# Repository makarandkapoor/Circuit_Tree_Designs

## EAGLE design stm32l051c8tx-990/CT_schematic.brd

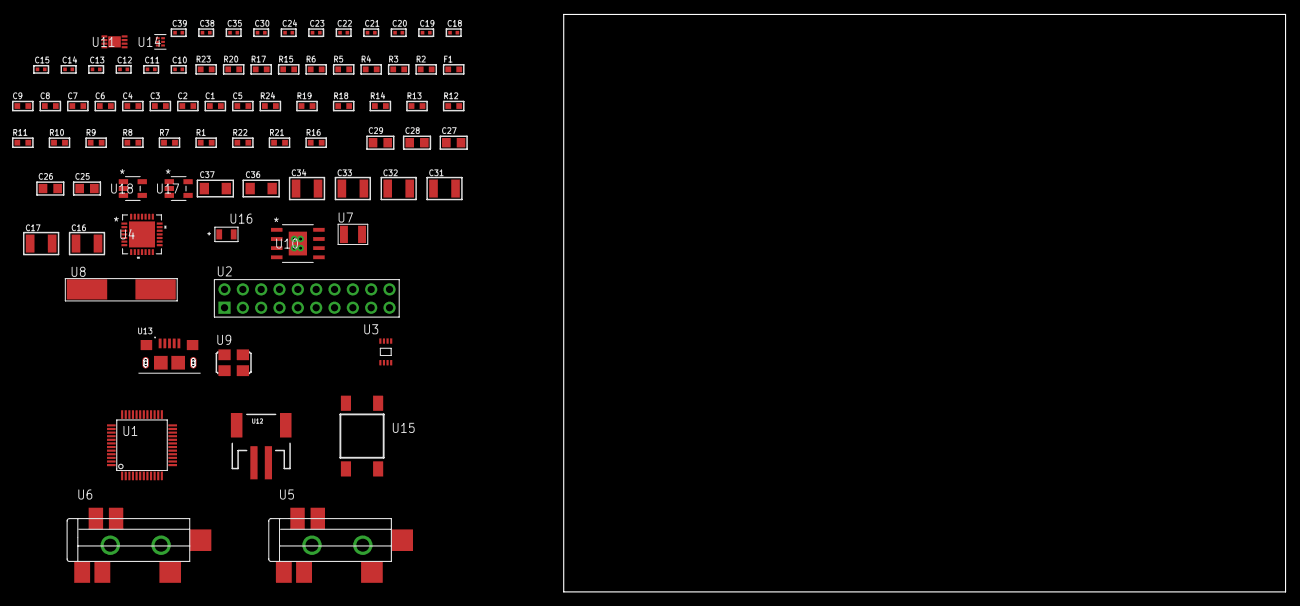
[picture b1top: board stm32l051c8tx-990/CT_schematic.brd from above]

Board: 2 copper layers, 82 parts (0 on the bottom side), 37 nets, no tracks yet.

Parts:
C1, C2, C3, C4, C6, C7: 1e-07; C0603
C5: 4.7e-06; C0603
C8: 1e-08; C0603
C9: 1e-06; C0603
C10, C11, C12, C13: 1e-11; C0402
C14, C20, C21, C22, C23, C24, C35: 1e-07; C0402
C15, C30, C38, C39: 1e-08; C0402
C16, C17: 2.2e-05; C1210
C18, C19: 1e-09; C0402
C25, C26, C27, C28, C29: 1e-05; C0805
C31, C32, C33, C34: 1e-05; C1210
C36, C37: 1e-05; C1206
F1: 240.0; L0603
R1, R7, R8, R9, R10, R11, R18, R19, R24: 10000.0; R0603
R2: 1000.0; R0603
R3: 1600.5; R0603
R4: 4700.0; R0603
R5, R6, R17: 2200.0; R0603
R12, R13, R14: 47000.0; R0603
R15: 680.0; R0603
R16: 4031.5447154472; R0603
R20: 9100.0; R0603
R21: 680000.0; R0603
R22: 120000.0; R0603
R23: 2000.0; R0603
U1: STM32L051C8T3; LQFP48
U2: TST-110-05-T-D-RA
U3: 24AA128T-I/MNY; TDFN-8/6MM
U4: WM8731CLSEFL; QFN-28
U5, U6: SJ-43515TS-SMT-TR
U7: ABS07-32.768KHZ-7-T
U8: ABLS-25.000MHZ-B2F-T
U9: ASFL1-12.288MHZ-EC-T; ASFL1
U10: MIC5234YME; SOIC-8_EP
U11: MCP73831T-2ACI/MC; DFN8_2X3MC
U12: S2B-PH-SM4-TB(LF)(SN); JST-2-SMD
U13: 10118193-0001LF; FCI_10118193-0001LF
U14: TPS3895ADRYR; SON-6
U15: 4-1437565-2; SW_4-1437565-2
U16: Q65110A2395; LGM67K-G1J2-24-Z
U17, U18: nc7sz125m5x; NC7SZ125M5X

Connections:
CLK_CRYSTAL_U1_3: C10.1, U1.3, U7.1
CLK_CRYSTAL_U1_4: C11.1, U1.4, U7.2
CLK_CRYSTAL_U1_5: C12.1, U1.5, U8.1
CLK_CRYSTAL_U1_6: C13.1, U1.6, U8.2
CLK_U4_1: U4.1, U9.3
GND: C1.2, C2.2, C3.2, C4.2, C5.2, C6.2, C7.2, C8.2, C9.2, C10.2, C11.2, C12.2, C13.2, C14.2, C15.2, C19.2, C20.2, C21.2, C22.2, C23.2, C24.2, C25.2, C26.2, C27.2, C28.2, C29.2, C30.2, C31.2, C32.2, C33.2, C34.2, C35.2, C36.2, C37.2, C38.2, C39.2, R2.2, R7.2, R9.2, R10.2, R12.2, R13.2, R14.2, R17.2, R20.2, R22.2, R23.2, U1.8, U1.23, U1.35, U1.47, U2.4, U2.6, U2.8, U2.10, U2.12, U2.14, U2.16, U2.18, U2.20, U3.4, U4.4, U4.15, U4.19, U4.25, U4.26, U4.29, U5.1, U6.1, U9.2, U10.7, U10.EPAD, U11.6, U11.9, U12.2, U13.5, U13.6, U13.7, U13.8, U13.9, U14.2, U16.C, U17.2, U17.3, U18.1, U18.3
INPUT_USBPOWER_5V: C36.1, R24.2, U11.1, U11.2, U13.1
NET_U1_7: R4.1, U1.7, U18.4
NET_U1_9: C8.1, C9.1, F1.1, U1.9
NET_U1_36: C6.1, C7.1, U1.36
NET_U1_42: R5.1, U1.42, U3.6
NET_U1_43: R6.1, U1.43, U3.5
NET_U1_44: R7.1, U1.44
NET_U1_45: R3.1, U1.45, U16.A
NET_U1_46: R1.1, U1.46, U15.3, U15.4
NET_U3_1: R9.1, U3.1
NET_U3_2: R10.1, U3.2
NET_U3_3: R11.1, U3.3
NET_U4_20: C24.1, C29.1, U4.20
NET_U5_2: C17.1, R13.1, U5.2
NET_U5_5: C16.1, R12.1, U5.5
NET_U6_5: C18.1, C19.1, R14.1, R15.1, U6.5
NET_U10_4: R16.2, R17.1, U10.4
NET_U11_5: R24.1, U11.5
NET_U11_8: R23.1, U11.8
NET_U14_1: R19.1, R20.1, U14.1
NET_U14_3: R21.2, R22.1, U14.3
NET_U14_4: R18.1, U14.4, U17.4, U18.2
NET_U15_1: R2.1, U15.1, U15.2
PROC_I2S2_CK: U1.26, U4.7
PROC_I2S2_SD: U1.28, U4.8
PROC_I2S2_WS: U1.25, U4.9, U4.11
PROC_SYS_SWCLK: U1.37, U2.9
PROC_SYS_SWDIO: U1.34, U2.7
RST_OUT_U2_SRESET_B: R8.1, U2.15, U17.1
VCC_S1_3V7: C31.1, C32.1, C37.1, U10.5, U10.8, U11.3, U11.4, U12.1
VCC_TIER1_3V3: C1.1, C2.1, C3.1, C4.1, C5.1, C14.1, C15.1, C20.1, C21.1, C22.1, C23.1, C25.1, C26.1, C27.1, C28.1, C30.1, C33.1, C34.1, C35.1, C38.1, C39.1, F1.2, R1.2, R3.2, R4.2, R5.2, R6.2, R8.2, R11.2, R16.1, R18.2, R19.2, R21.1, U1.1, U1.24, U1.48, U2.1, U3.7, U3.8, U4.3, U4.5, U4.12, U4.18, U9.4, U10.1, U14.6, U17.5, U18.5

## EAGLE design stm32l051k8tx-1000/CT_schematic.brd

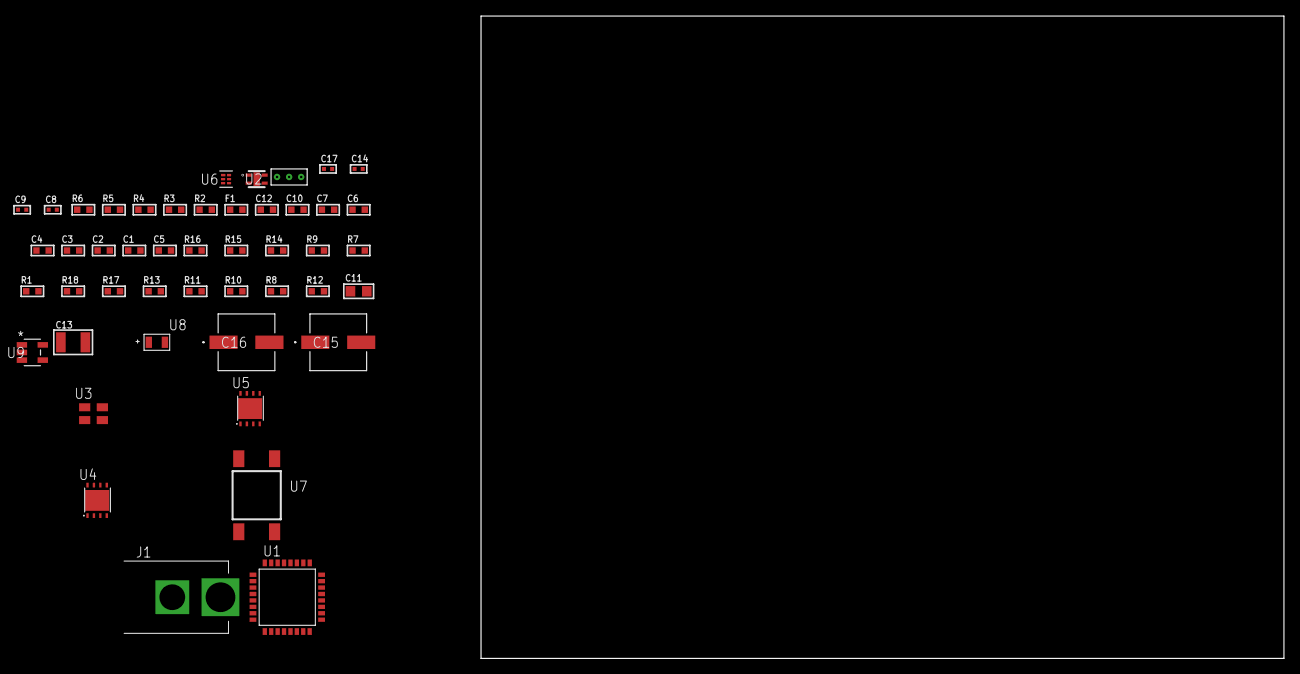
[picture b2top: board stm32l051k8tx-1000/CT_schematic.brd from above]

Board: 2 copper layers, 100.0 x 80.0 mm, 47 parts (0 on the bottom side), 22 nets, no tracks yet.

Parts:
C1, C2, C3, C4: 1e-07; C0603
C5: 4.7e-06; C0603
C6: 1e-08; C0603
C7: 1e-06; C0603
C8, C14: 1e-07; C0402
C9, C17: 1e-08; C0402
C10, C12: 8e-07; R0603
C11: 1e-05; C0805
C13: 1e-05; C1210
C15, C16: 0.0001; EXV-9H
F1: 240.0; L0603
J1: PJ-037B; PJ-037B_PACKAGE
R1, R7, R14, R15: 10000.0; R0603
R2: 1000.0; R0603
R3: 910.0; R0603
R4: 4700.0; R0603
R5, R6: 2200.0; R0603
R8, R10, R11, R13: 100000.0; R0603
R9: 36000.0; R0603
R12: 153694.38; R0603
R16: 82000.0; R0603
R17: 300000.0; R0603
R18: 120000.0; R0603
U1: STM32L051K8T6; LQFP32
U2: Si7034-A10-IM; SI7034-A10-IM
U3: ASEK-32.768KHz-ECST; ASEK
U4, U5: LP2951ACSDX/NOPB; WSON-8
U6: TPS3895ADRYR; SON-6
U7: 4-1437565-2; SW_4-1437565-2
U8: Q65110A2395; LGM67K-G1J2-24-Z
U9: nc7sz125m5x; NC7SZ125M5X
U10: Dummy; DUMMY_PACKAGE_99

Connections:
CLK_U1_2: U1.2, U3.3
GND: C1.2, C2.2, C3.2, C4.2, C5.2, C6.2, C7.2, C8.2, C9.2, C10.2, C11.2, C12.2, C13.2, C14.2, C15.2, C16.2, C17.2, J1.2, R2.2, R7.2, R10.2, R13.2, R16.2, R18.2, U1.16, U1.32, U2.5, U3.2, U4.3, U4.4, U4.PAD, U5.3, U5.4, U5.PAD, U6.2, U8.C, U9.1, U9.3, U10.1
NET_U1_4: R4.1, U1.4, U9.4
NET_U1_5: C6.1, C7.1, F1.1, U1.5
NET_U1_27: R3.1, U1.27, U8.A
NET_U1_28: R1.1, U1.28, U7.3, U7.4
NET_U1_29: R5.1, U1.29, U2.2
NET_U1_30: R6.1, U1.30, U2.4
NET_U1_31: R7.1, U1.31
NET_U4_5: R8.1, U4.5
NET_U4_7: R9.2, R10.1, U4.7
NET_U5_5: R11.1, U5.5
NET_U5_7: R12.2, R13.1, U5.7
NET_U6_1: R15.1, R16.1, U6.1
NET_U6_3: R17.2, R18.1, U6.3
NET_U6_4: R14.1, U6.4, U9.2
NET_U7_1: R2.1, U7.1, U7.2
PROC_ADC_IN4: U1.10, U10.2
PROC_ADC_IN6: U1.12, U10.3
VCC_S1_15V5: C10.1, C12.1, C15.1, C16.1, J1.1, U4.8, U5.8
VCC_TIER1_1V8: C1.1, C2.1, C3.1, C4.1, C5.1, C8.1, C11.1, C14.1, C17.1, F1.2, R1.2, R3.2, R4.2, R5.2, R6.2, R8.2, R9.1, R14.2, R15.2, R17.1, U1.1, U1.17, U2.1, U4.1, U6.6, U9.5
VCC_TIER1_3V3: C9.1, C13.1, R11.2, R12.1, U3.4, U5.1

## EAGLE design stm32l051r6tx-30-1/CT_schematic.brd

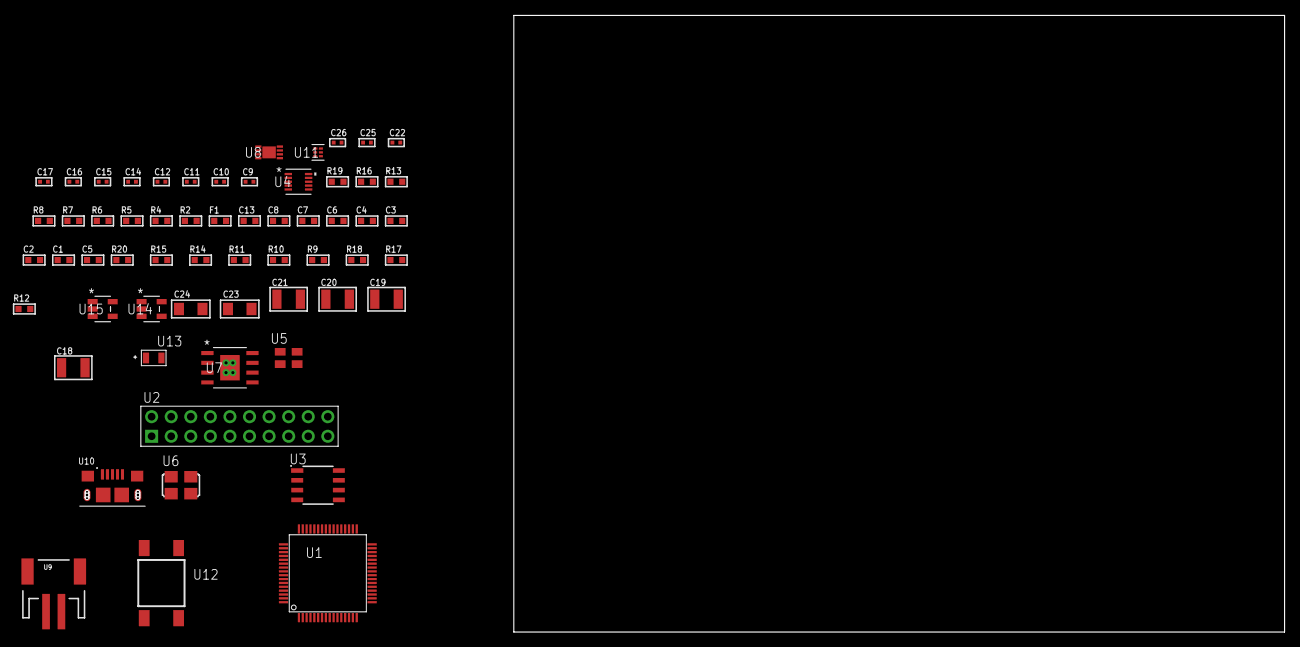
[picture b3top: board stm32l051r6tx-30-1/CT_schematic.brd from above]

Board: 2 copper layers, 155.6 x 80.0 mm, 60 parts (0 on the bottom side), 27 nets, no tracks yet.

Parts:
C1, C2, C3, C4, C6: 1e-07; C0603
C5: 4.7e-06; C0603
C7: 1e-08; C0603
C8, C13: 1e-06; C0603
C9, C11, C12, C14, C15, C22: 1e-07; C0402
C10, C16, C17, C25, C26: 1e-08; C0402
C18, C19, C20, C21: 1e-05; C1210
C23, C24: 1e-05; C1206
F1: 240.0; L0603
R2: 1000.0; R0603
R4: 4700.0; R0603
R5, R6, R7, R8, R13: 2200.0; R0603
R9, R10, R11, R14, R15, R20: 10000.0; R0603
R12: 4031.5447154472; R0603
R16: 9100.0; R0603
R17: 680000.0; R0603
R18: 120000.0; R0603
R19: 2000.0; R0603
U1: STM32L051R6T6; LQFP64
U2: TST-110-05-T-D-RA
U3: M24M02-DRMN6TP; SOIC-8
U4: MAG3110FCR1; DFN-10
U5: ASEK-32.768KHz-ECST; ASEK
U6: ASFL1-25MHZ-NCS; ASFL1
U7: MIC5234YME; SOIC-8_EP
U8: MCP73831T-2ACI/MC; DFN8_2X3MC
U9: S2B-PH-SM4-TB(LF)(SN); JST-2-SMD
U10: 10118193-0001LF; FCI_10118193-0001LF
U11: TPS3895ADRYR; SON-6
U12: 4-1437565-2; SW_4-1437565-2
U13: Q65110A2395; LGM67K-G1J2-24-Z
U14, U15: nc7sz125m5x; NC7SZ125M5X

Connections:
CLK_U1_3: U1.3, U5.3
CLK_U1_5: U1.5, U6.3
GND: C1.2, C2.2, C3.2, C4.2, C5.2, C6.2, C7.2, C8.2, C9.2, C10.2, C11.2, C12.2, C13.2, C14.2, C15.2, C16.2, C17.2, C18.2, C19.2, C20.2, C21.2, C22.2, C23.2, C24.2, C25.2, C26.2, R2.2, R9.2, R11.2, R13.2, R16.2, R18.2, R19.2, U1.12, U1.18, U1.31, U1.47, U1.63, U2.4, U2.6, U2.8, U2.10, U2.12, U2.14, U2.16, U2.18, U2.20, U3.4, U4.5, U4.10, U5.2, U6.2, U7.7, U7.EPAD, U8.6, U8.9, U9.2, U10.5, U10.6, U10.7, U10.8, U10.9, U11.2, U13.C, U14.2, U14.3, U15.1, U15.3
INPUT_USBPOWER_5V: C23.1, R20.2, U8.1, U8.2, U10.1
NET_U1_7: R4.1, U1.7, U15.4
NET_U1_13: C7.1, C8.1, F1.1, U1.13
NET_U1_29: R7.1, U1.29, U3.6
NET_U1_30: R8.1, U1.30, U3.5
NET_U1_58: R5.1, U1.58, U4.7
NET_U1_59: R6.1, U1.59, U4.6
NET_U1_60: R9.1, U1.60
NET_U1_62: U12.3, U12.4
NET_U3_3: R11.1, U3.3
NET_U4_1: C11.1, U4.1
NET_U4_4: C14.1, U4.4
NET_U7_4: R12.2, R13.1, U7.4
NET_U8_5: R20.1, U8.5
NET_U8_8: R19.1, U8.8
NET_U11_1: R15.1, R16.1, U11.1
NET_U11_3: R17.2, R18.1, U11.3
NET_U11_4: R14.1, U11.4, U14.4, U15.2
NET_U12_1: R2.1, U12.1, U12.2
PROC_SYS_SWCLK: U1.49, U2.9
PROC_SYS_SWDIO: U1.46, U2.7
RST_OUT_U2_SRESET_B: R10.1, U2.15, U14.1
VCC_S1_3V7: C18.1, C19.1, C24.1, U7.5, U7.8, U8.3, U8.4, U9.1
VCC_TIER1_3V3: C1.1, C2.1, C3.1, C4.1, C5.1, C6.1, C9.1, C10.1, C12.1, C13.1, C15.1, C16.1, C17.1, C20.1, C21.1, C22.1, C25.1, C26.1, F1.2, R4.2, R5.2, R6.2, R7.2, R8.2, R10.2, R12.1, R14.2, R15.2, R17.1, U1.1, U1.19, U1.32, U1.48, U1.64, U2.1, U3.8, U4.2, U4.8, U5.4, U6.4, U7.1, U11.6, U14.5, U15.5

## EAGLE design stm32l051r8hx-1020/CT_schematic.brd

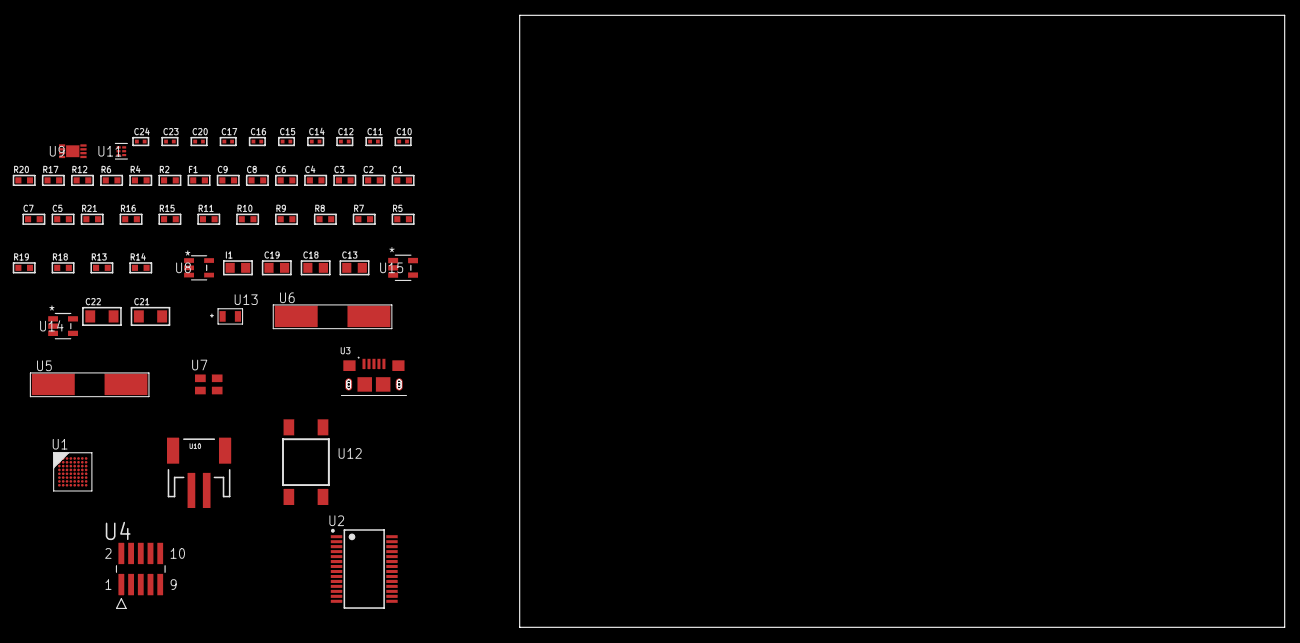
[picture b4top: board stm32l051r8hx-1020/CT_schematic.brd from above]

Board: 2 copper layers, 122.6 x 80.0 mm, 60 parts (0 on the bottom side), 35 nets, no tracks yet.

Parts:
C1, C2, C3, C4, C6: 1e-07; C0603
C5, C7: 4.7e-06; C0603
C8: 1e-08; C0603
C9: 1e-06; C0603
C10, C11: 1e-11; C0402
C12, C14, C15, C16, C20: 1e-07; C0402
C13: 4.7e-06; C0805
C17, C23, C24: 1e-08; C0402
C18, C19: 1e-05; C0805
C21, C22: 1e-05; C1206
F1: 240.0; L0603
I1: 2.2e-06; L0805
R2: 1000.0; R0603
R4, R6: 4700.0; R0603
R5, R7, R8, R9, R10, R11, R15, R16, R21: 10000.0; R0603
R12: 5.0; R0603
R13: 220000.0; R0603
R14: 1000000.0; R0603
R17: 9100.0; R0603
R18: 680000.0; R0603
R19: 120000.0; R0603
R20: 2000.0; R0603
U1: STM32L051R8H7; TFBGA64
U2: FT232RL-REEL; SSOP-28
U3: 10118193-0001LF; FCI_10118193-0001LF
U4: FTSH-105-01-L-DV-K; SAMTEC_FTSH-105-01-L-DV-K
U5: ABLS-25.000MHZ-B2F-T
U6: ABLS-12.000MHZ-B4-T
U7: ASEK-32.768KHz-ECST; ASEK
U8: ltc3406es5; TSOT-23-5
U9: MCP73831T-2ACI/MC; DFN8_2X3MC
U10: S2B-PH-SM4-TB(LF)(SN); JST-2-SMD
U11: TPS3895ADRYR; SON-6
U12: 4-1437565-2; SW_4-1437565-2
U13: Q65110A2395; LGM67K-G1J2-24-Z
U14, U15: nc7sz125m5x; NC7SZ125M5X

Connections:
CLK_CRYSTAL_U1_C1: C10.1, U1.C1, U5.1
CLK_CRYSTAL_U1_D1: C11.1, U1.D1, U5.2
CLK_CRYSTAL_U2_27: U2.27, U6.1
CLK_CRYSTAL_U2_28: U2.28, U6.2
CLK_U1_A1: U1.A1, U7.3
GND: C1.2, C2.2, C3.2, C4.2, C5.2, C6.2, C7.2, C8.2, C9.2, C10.2, C11.2, C12.2, C13.2, C14.2, C15.2, C16.2, C17.2, C18.2, C19.1, C19.2, C20.2, C21.2, C22.2, C23.2, C24.2, R2.2, R5.2, R8.2, R12.2, R13.2, R17.2, R19.2, R20.2, U1.C2, U1.D4, U1.D5, U1.D6, U1.F1, U2.7, U2.18, U2.21, U2.25, U2.26, U3.5, U3.6, U3.7, U3.8, U3.9, U4.3, U4.5, U7.2, U8.2, U9.6, U9.9, U10.2, U11.2, U13.C, U14.2, U14.3, U15.1, U15.3
INPUT_USBPOWER_5V: C21.1, R6.1, R21.2, U3.1, U9.1, U9.2
NET_U1_B4: R5.1, U1.B4
NET_U1_E1: R4.1, U1.E1, U15.4
NET_U1_H1: C8.1, C9.1, F1.1, U1.G1, U1.H1
NET_U1_H8: U12.3, U12.4
NET_U2_14: R7.1, U2.14
NET_U2_17: C14.1, U2.17
NET_U2_19: R8.1, U2.19
NET_U3_2: U2.16, U3.2
NET_U3_3: U2.15, U3.3
NET_U4_9: R12.1, U4.9
NET_U8_3: I1.1, U8.3
NET_U8_5: R13.1, R14.1, U8.5
NET_U8_ATNET_3: I1.2, R14.2
NET_U9_5: R21.1, U9.5
NET_U9_8: R20.1, U9.8
NET_U11_1: R16.1, R17.1, U11.1
NET_U11_3: R18.2, R19.1, U11.3
NET_U11_4: R15.1, U11.4, U14.4, U15.2
NET_U12_1: R2.1, U12.1, U12.2
PROC_LPUART1_CTS: U1.G4, U2.3
PROC_LPUART1_RTS: U1.B5, U2.11
PROC_LPUART1_RX: U1.B6, U2.1
PROC_LPUART1_TX: U1.B7, U2.5
PROC_SYS_SWCLK: R10.1, U1.A7, U4.4
PROC_SYS_SWDIO: R11.1, U1.A8, U4.2
RST_OUT_U4_JTAG_RST_B: R9.1, U4.10, U14.1
VCC_S1_3V7: C18.1, C22.1, U8.4, U9.3, U9.4, U10.1
VCC_TIER1_3V3: C1.1, C2.1, C3.1, C4.1, C5.1, C6.1, C7.1, C12.1, C13.1, C15.1, C16.1, C17.1, C19.2, C20.1, C23.1, C24.1, F1.2, I1.2, R4.2, R7.2, R9.2, R10.2, R11.2, R14.2, R15.2, R16.2, R18.1, U1.B2, U1.D2, U1.E4, U1.E5, U1.E6, U2.4, U2.20, U4.1, U7.4, U11.6, U14.5, U15.5

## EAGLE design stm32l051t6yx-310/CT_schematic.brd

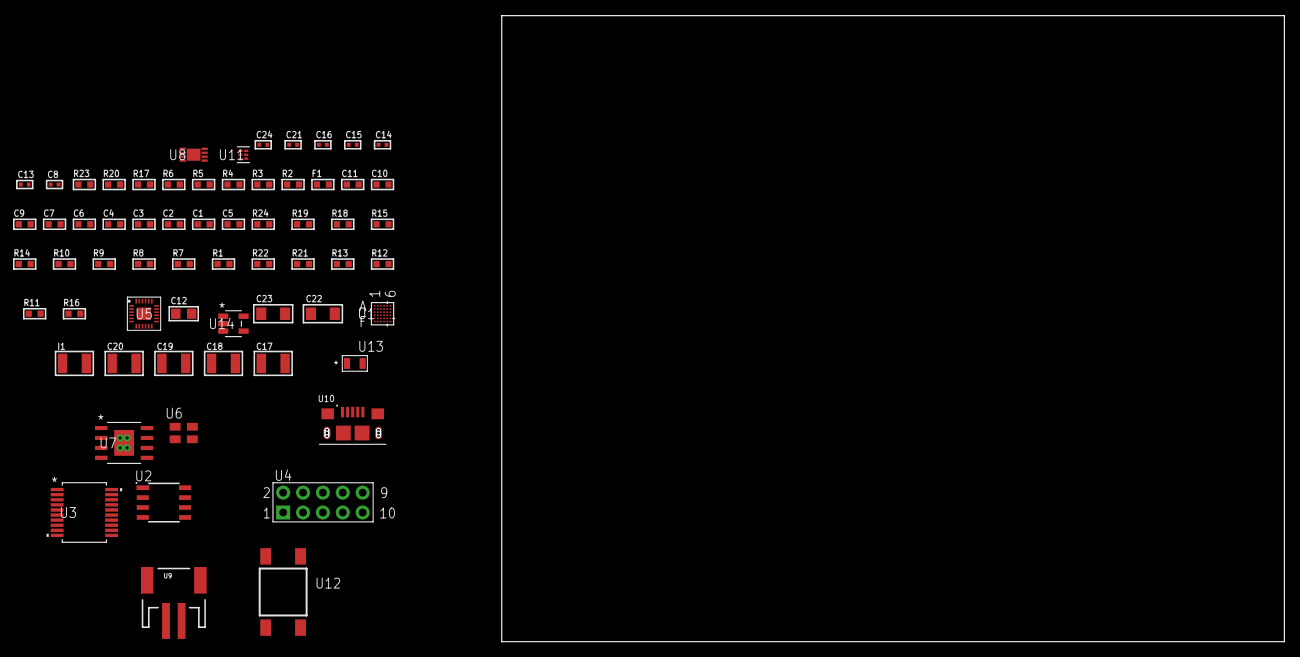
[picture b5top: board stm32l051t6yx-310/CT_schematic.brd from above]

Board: 2 copper layers, 122.6 x 80.0 mm, 64 parts (0 on the bottom side), 46 nets, no tracks yet.

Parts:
C1, C2, C3, C4: 1e-07; C0603
C5: 4.7e-06; C0603
C6: 1e-08; C0603
C7, C9, C10, C11: 1e-06; C0603
C8, C15, C16, C24: 1e-08; C0402
C12: 4.7e-06; C0805
C13, C14, C21: 1e-07; C0402
C17, C18, C19, C20: 1e-05; C1210
C22, C23: 1e-05; C1206
F1: 240.0; L0603
I1: 1.5e-05; L1210
R1, R7, R8, R9, R10, R14, R15, R18, R19, R24: 10000.0; R0603
R2: 1000.0; R0603
R3: 1600.5; R0603
R4: 4700.0; R0603
R5, R6, R17: 2200.0; R0603
R11, R12, R13: 100000.0; R0603
R16: 4031.5447154472; R0603
R20: 9100.0; R0603
R21: 680000.0; R0603
R22: 120000.0; R0603
R23: 2000.0; R0603
U1: STM32L051T6Y6TR; WLCSP36
U2: AT25256B-SSHL-T; SOIC-8
U3: MAX3218EAP+T; SSOP-20
U4: HTSS-105-01-G-D
U5: MPU-9250; QFN24_2
U6: ASEK-32.768KHz-ECST; ASEK
U7: MIC5234YME; SOIC-8_EP
U8: MCP73831T-2ACI/MC; DFN8_2X3MC
U9: S2B-PH-SM4-TB(LF)(SN); JST-2-SMD
U10: 10118193-0001LF; FCI_10118193-0001LF
U11: TPS3895ADRYR; SON-6
U12: 4-1437565-2; SW_4-1437565-2
U13: Q65110A2395; LGM67K-G1J2-24-Z
U14: nc7sz125m5x; NC7SZ125M5X

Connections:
CLK_U1_A6: U1.A6, U6.3
GND: C1.2, C2.2, C3.2, C4.2, C5.2, C6.2, C7.2, C8.2, C9.2, C10.2, C11.2, C13.2, C14.2, C15.2, C16.2, C17.2, C18.2, C19.2, C20.2, C21.2, C22.2, C23.2, C24.2, R2.2, R7.2, R17.2, R20.2, R22.2, R23.2, U1.D6, U2.4, U3.5, U3.17, U3.20, U4.9, U5.18, U5.20, U5.25, U6.2, U7.7, U7.EPAD, U8.6, U8.9, U9.2, U10.5, U10.6, U10.7, U10.8, U10.9, U11.2, U13.C, U14.1, U14.3
INPUT_USBPOWER_5V: C22.1, R24.2, U8.1, U8.2, U10.1
NET_U1_A4: R6.1, U1.A4, U5.24
NET_U1_B4: R5.1, U1.B4, U5.23
NET_U1_C5: R7.1, U1.C5
NET_U1_C6: R4.1, U1.C6, U14.4
NET_U1_D5: C6.1, C7.1, F1.1, U1.D5, U1.E6
NET_U1_F5: R3.1, U1.F5, U13.A
NET_U1_F6: R1.1, U1.F6, U12.3, U12.4
NET_U2_3: R8.1, U2.3
NET_U2_7: R10.1, U2.7
NET_U3_1: I1.1, U3.1
NET_U3_2: R11.1, U3.2
NET_U3_3: R12.1, U3.3
NET_U3_4: R13.1, U3.4
NET_U3_15: C11.1, U3.15
NET_U3_16: C12.2, U3.16
NET_U3_18: C12.1, U3.18
NET_U3_19: C10.1, U3.19
NET_U4_3: U3.12, U4.3
NET_U4_4: U3.11, U4.4
NET_U4_5: U3.14, U4.5
NET_U4_6: U3.13, U4.6
NET_U5_9: R15.1, U5.9
NET_U5_10: C13.1, U5.10
NET_U5_22: R14.1, U5.22
NET_U7_4: R16.2, R17.1, U7.4
NET_U8_5: R24.1, U8.5
NET_U8_8: R23.1, U8.8
NET_U11_1: R19.1, R20.1, U11.1
NET_U11_3: R21.2, R22.1, U11.3
NET_U11_4: R18.1, U11.4, U14.2
NET_U12_1: R2.1, U12.1, U12.2
PROC_GPIO_TO_U5_FSYNC: U1.B2, U5.11
PROC_GPIO_TO_U5_INT_B: U1.A1, U5.12
PROC_LPUART1_CTS: U1.E3, U3.8
PROC_LPUART1_RTS: U1.C3, U3.10
PROC_LPUART1_RX: U1.D2, U3.9
PROC_LPUART1_TX: U1.E2, U3.7
PROC_SPI1_MISO: U1.A3, U2.2
PROC_SPI1_MOSI: U1.B1, U2.5
PROC_SPI1_NSS: R9.1, U1.A2, U2.1
PROC_SPI1_SCK: U1.B3, U2.6
VCC_S1_3V7: C17.1, C18.1, C23.1, U7.5, U7.8, U8.3, U8.4, U9.1
VCC_TIER1_3V3: C1.1, C2.1, C3.1, C4.1, C5.1, C8.1, C9.1, C14.1, C15.1, C16.1, C19.1, C20.1, C21.1, C24.1, F1.2, I1.2, R1.2, R3.2, R4.2, R5.2, R6.2, R8.2, R9.2, R10.2, R11.2, R12.2, R13.2, R14.2, R15.2, R16.1, R18.2, R19.2, R21.1, U1.A5, U1.F1, U2.8, U3.6, U5.1, U5.8, U5.13, U6.4, U7.1, U11.6, U14.5

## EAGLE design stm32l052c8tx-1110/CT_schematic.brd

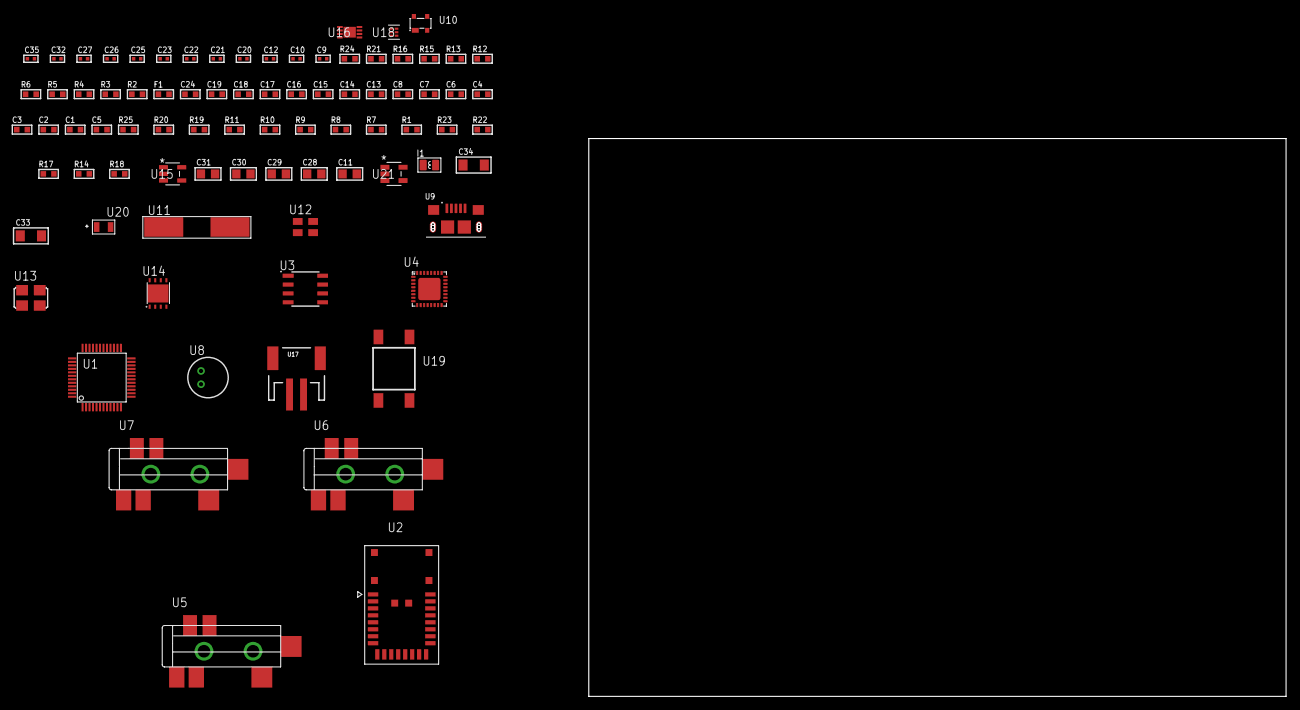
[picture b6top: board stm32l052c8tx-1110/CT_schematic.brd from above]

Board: 2 copper layers, 122.6 x 80.0 mm, 83 parts (0 on the bottom side), 54 nets, no tracks yet.

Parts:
C1, C2, C3, C4, C8: 1e-07; C0603
C5: 4.7e-06; C0603
C6: 1e-08; C0603
C7, C13, C14, C15, C16, C17, C18, C19, C24: 1e-06; C0603
C9, C10: 1e-11; C0402
C11, C28, C29, C30, C31: 1e-05; C0805
C12, C25, C26, C27, C35: 1e-08; C0402
C20, C21, C22, C23, C32: 1e-07; C0402
C33, C34: 1e-05; C1206
F1: 240.0; L0603
I1: 1.5e-06; L0806
R1, R7, R8, R9, R10, R11, R19, R20, R25: 10000.0; R0603
R2, R16: 1000.0; R0603
R3: 1600.5; R0603
R4: 4700.0; R0603
R5, R6: 2200.0; R0603
R12, R13: 1270.0; R0603
R14: 100000.0; R0603
R15: 200.0; R0603
R17: 220000.0; R0603
R18: 1000000.0; R0603
R21: 9100.0; R0603
R22: 680000.0; R0603
R23: 120000.0; R0603
R24: 2000.0; R0603
U1: STM32L052C8T6; LQFP48
U2: A2500R24A00GM
U3: AT24C02D-SSHM-T; AT24C02D
U4: SGTL5000XNAA3; QFN-32
U5, U6, U7: SJ-43515TS-SMT-TR
U8: WM-64PCT; WM-64PC
U9: 10118193-0001LF; FCI_10118193-0001LF
U10: prtr5v0u2ax; SOT143B
U11: ABLS-25.000MHZ-B2F-T
U12: ASEK-32.768KHz-ECST; ASEK
U13: ASFL-24.57MHZ-NCS; ASFL1
U14: LP3878SDX-ADJ/NOPB; WSON-8
U15: ltc3406es5; TSOT-23-5
U16: MCP73831T-2ACI/MC; DFN8_2X3MC
U17: S2B-PH-SM4-TB(LF)(SN); JST-2-SMD
U18: TPS3895ADRYR; SON-6
U19: 4-1437565-2; SW_4-1437565-2
U20: Q65110A2395; LGM67K-G1J2-24-Z
U21: nc7sz125m5x; NC7SZ125M5X

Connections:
CLK_CRYSTAL_U1_5: C9.1, U1.5, U11.1
CLK_CRYSTAL_U1_6: C10.1, U1.6, U11.2
CLK_U1_3: U1.3, U12.3
CLK_U4_21: U4.21, U13.3
GND: C1.2, C2.2, C3.2, C4.2, C5.2, C6.2, C7.2, C8.2, C9.2, C10.2, C11.2, C12.2, C20.2, C21.2, C22.2, C23.2, C24.2, C25.2, C26.2, C27.2, C28.2, C29.2, C30.2, C31.1, C31.2, C32.2, C33.2, C34.2, C35.2, R2.2, R7.2, R8.2, R10.2, R11.2, R13.2, R16.2, R17.2, R21.2, R23.2, R24.2, U1.8, U1.23, U1.35, U1.47, U2.8, U2.17, U3.4, U4.1, U4.3, U4.7, U4.EXP, U6.1, U7.1, U8.2, U9.5, U9.6, U9.7, U9.8, U9.9, U10.1, U12.2, U13.2, U14.3, U14.PAD, U15.2, U16.6, U16.9, U17.2, U18.2, U20.C, U21.1, U21.3
INPUT_USBPOWER_5V: C33.1, R25.2, U9.1, U10.4, U16.1, U16.2
NET_U1_7: R4.1, U1.7, U21.4
NET_U1_9: C6.1, C7.1, F1.1, U1.9
NET_U1_42: R5.1, U1.42, U3.6
NET_U1_43: R6.1, U1.43, U3.5
NET_U1_44: R7.1, U1.44
NET_U1_45: R3.1, U1.45, U20.A
NET_U1_46: R1.1, U1.46, U19.3, U19.4
NET_U3_1: R9.1, U3.1
NET_U3_2: R10.1, U3.2
NET_U3_3: R11.1, U3.3
NET_U3_7: R8.1, U3.7
NET_U4_10: C23.1, U4.10
NET_U4_29: R12.1, U4.29
NET_U4_31: R13.1, U4.31
NET_U5_1: U4.4, U5.1
NET_U5_2: U4.2, U5.2
NET_U5_5: U4.6, U5.5
NET_U6_2: C14.1, U6.2
NET_U6_5: C13.1, U6.5
NET_U7_2: C16.1, C17.1, U7.2
NET_U7_5: C15.1, U7.5
NET_U7_13: C16.2, C17.2
NET_U8_1: C18.1, C19.1, C24.1, U4.16, U8.1
NET_U8_15: C18.2, C19.2
NET_U14_1: C27.1, U14.1
NET_U14_6: R15.2, R16.1, U14.6
NET_U14_8: R14.1, U14.8
NET_U15_3: I1.1, U15.3
NET_U15_5: R17.1, R18.1, U15.5
NET_U15_ATNET_3: I1.2, R18.2
NET_U16_5: R25.1, U16.5
NET_U16_8: R24.1, U16.8
NET_U18_1: R20.1, R21.1, U18.1
NET_U18_3: R22.2, R23.1, U18.3
NET_U18_4: R19.1, U18.4, U21.2
NET_U19_1: R2.1, U19.1, U19.2
PROC_I2S2_CK: U1.26, U4.24
PROC_I2S2_SD: U1.28, U4.26
PROC_I2S2_WS: U1.25, U4.23
PROC_SPI1_MISO: U1.16, U2.10
PROC_SPI1_MOSI: U1.17, U2.11
PROC_SPI1_NSS: U1.14, U2.12
PROC_SPI1_SCK: U1.15, U2.9
PROC_USB_DM: U1.32, U9.2, U10.3
PROC_USB_DP: U1.33, U9.3, U10.2
VCC_S1_3V7: C28.1, C30.1, C34.1, R14.2, U14.4, U15.4, U16.3, U16.4, U17.1
VCC_TIER1_1V2: C20.1, C29.1, R15.1, U4.30, U14.5
VCC_TIER1_3V3: C1.1, C2.1, C3.1, C4.1, C5.1, C8.1, C11.1, C12.1, C21.1, C22.1, C25.1, C26.1, C31.2, C32.1, C35.1, F1.2, I1.2, R1.2, R3.2, R4.2, R5.2, R6.2, R9.2, R12.2, R18.2, R19.2, R20.2, R22.1, U1.1, U1.24, U1.36, U1.48, U2.18, U3.8, U4.5, U4.20, U12.4, U13.4, U18.6, U21.5

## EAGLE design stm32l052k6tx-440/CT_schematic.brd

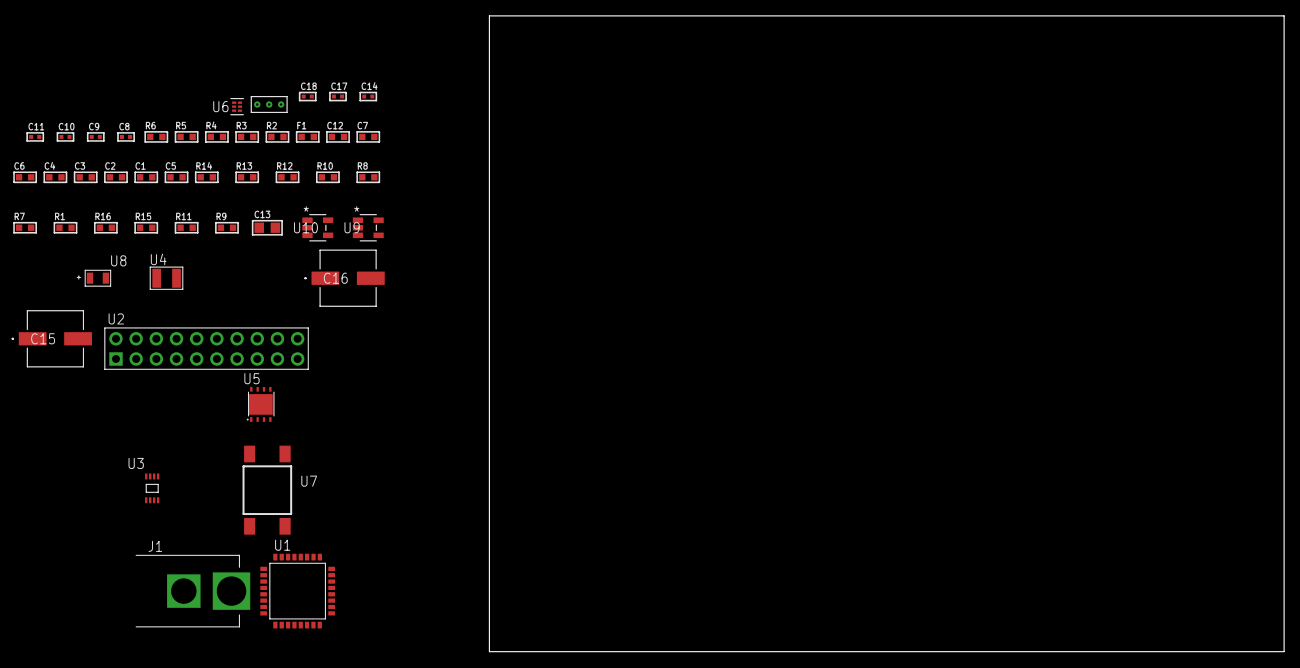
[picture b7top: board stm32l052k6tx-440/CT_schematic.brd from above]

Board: 2 copper layers, 100.0 x 80.0 mm, 47 parts (0 on the bottom side), 23 nets, no tracks yet.

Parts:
C1, C2, C3, C4: 1e-07; C0603
C5: 4.7e-06; C0603
C6: 1e-08; C0603
C7: 1e-06; C0603
C8, C9: 1e-11; C0402
C10, C14: 1e-07; C0402
C11, C17, C18: 1e-08; C0402
C12: 8e-07; R0603
C13: 1e-05; C0805
C15, C16: 0.0001; EXV-9H
F1: 240.0; L0603
J1: PJ-037B; PJ-037B_PACKAGE
R1, R7, R8, R12, R13: 10000.0; R0603
R2: 1000.0; R0603
R3: 910.0; R0603
R4: 4700.0; R0603
R5, R6: 2200.0; R0603
R9, R11: 100000.0; R0603
R10: 36000.0; R0603
R14: 82000.0; R0603
R15: 300000.0; R0603
R16: 120000.0; R0603
U1: STM32L052K6T6; LQFP32
U2: TST-110-05-T-D-RA
U3: 24AA01T-I/MNY; TDFN-8/6MM
U4: ABS07-32.768KHZ-7-T
U5: LP2951ACSDX/NOPB; WSON-8
U6: TPS3895ADRYR; SON-6
U7: 4-1437565-2; SW_4-1437565-2
U8: Q65110A2395; LGM67K-G1J2-24-Z
U9, U10: nc7sz125m5x; NC7SZ125M5X
U11: Dummy; DUMMY_PACKAGE_98

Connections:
CLK_CRYSTAL_U1_2: C8.1, U1.2, U4.1
CLK_CRYSTAL_U1_3: C9.1, U1.3, U4.2
GND: C1.2, C2.2, C3.2, C4.2, C5.2, C6.2, C7.2, C8.2, C9.2, C10.2, C11.2, C12.2, C13.2, C14.2, C15.2, C16.2, C17.2, C18.2, J1.2, R2.2, R7.2, R11.2, R14.2, R16.2, U1.16, U1.32, U2.4, U2.6, U2.8, U2.10, U2.12, U2.14, U2.16, U2.18, U2.20, U3.4, U5.3, U5.4, U5.PAD, U6.2, U8.C, U9.2, U9.3, U10.1, U10.3, U11.1
NET_U1_4: R4.1, U1.4, U10.4
NET_U1_5: C6.1, C7.1, F1.1, U1.5
NET_U1_27: R3.1, U1.27, U8.A
NET_U1_28: R1.1, U1.28, U7.3, U7.4
NET_U1_29: R5.1, U1.29, U3.6
NET_U1_30: R6.1, U1.30, U3.5
NET_U1_31: R7.1, U1.31
NET_U5_5: R9.1, U5.5
NET_U5_7: R10.2, R11.1, U5.7
NET_U6_1: R13.1, R14.1, U6.1
NET_U6_3: R15.2, R16.1, U6.3
NET_U6_4: R12.1, U6.4, U9.4, U10.2
NET_U7_1: R2.1, U7.1, U7.2
PROC_ADC_IN4: U1.10, U11.2
PROC_ADC_IN6: U1.12, U11.3
PROC_SYS_SWCLK: U1.24, U2.9
PROC_SYS_SWDIO: U1.23, U2.7
RST_OUT_U2_SRESET_B: R8.1, U2.15, U9.1
VCC_S1_13V5: C12.1, C15.1, C16.1, J1.1, U5.8
VCC_TIER1_1V8: C1.1, C2.1, C3.1, C4.1, C5.1, C10.1, C11.1, C13.1, C14.1, C17.1, C18.1, F1.2, R1.2, R3.2, R4.2, R5.2, R6.2, R8.2, R9.2, R10.1, R12.2, R13.2, R15.1, U1.1, U1.17, U2.1, U3.7, U3.8, U5.1, U6.6, U9.5, U10.5

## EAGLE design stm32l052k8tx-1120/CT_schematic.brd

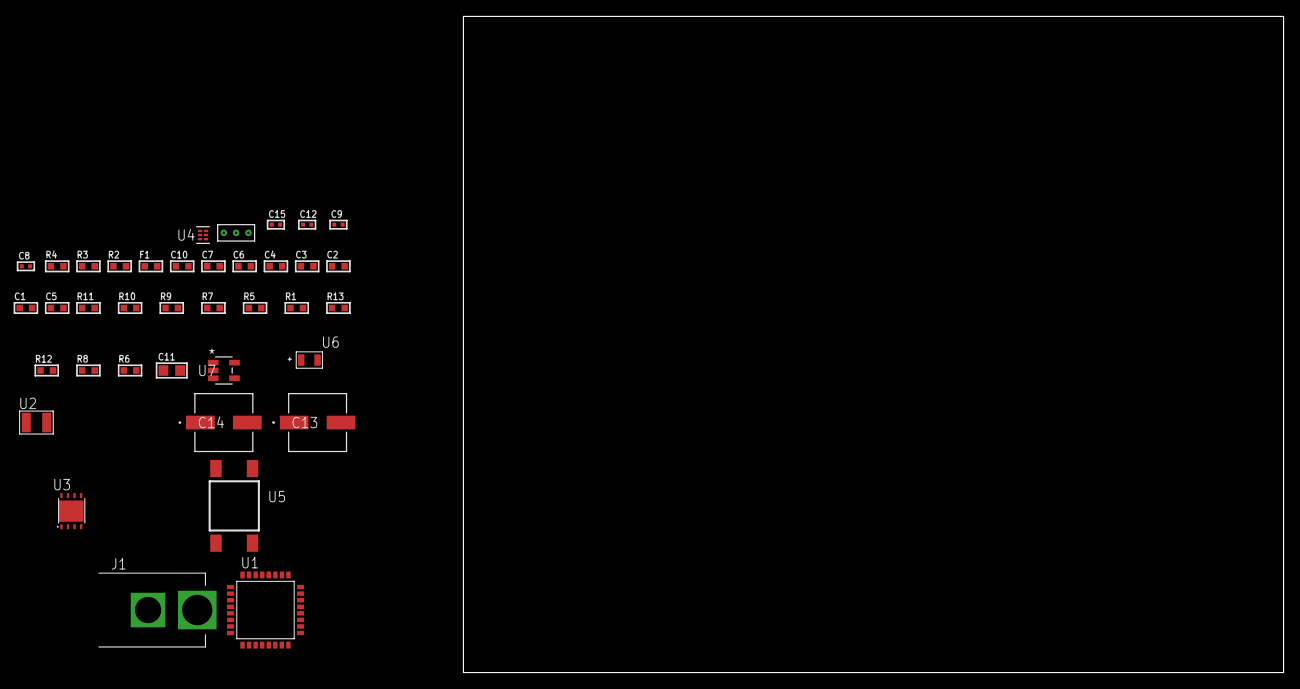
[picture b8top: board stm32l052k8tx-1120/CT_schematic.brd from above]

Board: 2 copper layers, 100.0 x 80.0 mm, 38 parts (0 on the bottom side), 18 nets, no tracks yet.

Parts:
C1, C2, C3, C4: 1e-07; C0603
C5: 4.7e-06; C0603
C6: 1e-08; C0603
C7, C10: 1e-06; C0603
C8, C9: 1e-11; C0402
C11: 1e-05; C0805
C12: 1e-07; C0402
C13, C14: 0.0001; EXV-9H
C15: 1e-08; C0402
F1: 240.0; L0603
J1: PJ-037B; PJ-037B_PACKAGE
R1, R5, R9, R10: 10000.0; R0603
R2: 1000.0; R0603
R3: 910.0; R0603
R4: 4700.0; R0603
R6, R8: 100000.0; R0603
R7: 36000.0; R0603
R11: 82000.0; R0603
R12: 300000.0; R0603
R13: 120000.0; R0603
U1: STM32L052K8T7; LQFP32
U2: ABS07-32.768KHZ-7-T
U3: LP2951ACSDX/NOPB; WSON-8
U4: TPS3895ADRYR; SON-6
U5: 4-1437565-2; SW_4-1437565-2
U6: Q65110A2395; LGM67K-G1J2-24-Z
U7: nc7sz125m5x; NC7SZ125M5X
U8: Dummy; DUMMY_PACKAGE_74

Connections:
CLK_CRYSTAL_U1_2: C8.1, U1.2, U2.1
CLK_CRYSTAL_U1_3: C9.1, U1.3, U2.2
GND: C1.2, C2.2, C3.2, C4.2, C5.2, C6.2, C7.2, C8.2, C9.2, C10.2, C11.2, C12.2, C13.2, C14.2, C15.2, J1.2, R2.2, R5.2, R8.2, R11.2, R13.2, U1.16, U1.32, U3.3, U3.4, U3.PAD, U4.2, U6.C, U7.1, U7.3, U8.1
NET_U1_4: R4.1, U1.4, U7.4
NET_U1_5: C6.1, C7.1, F1.1, U1.5
NET_U1_29: R3.1, U1.29, U6.A
NET_U1_30: R1.1, U1.30, U5.3, U5.4
NET_U1_31: R5.1, U1.31
NET_U3_5: R6.1, U3.5
NET_U3_7: R7.2, R8.1, U3.7
NET_U4_1: R10.1, R11.1, U4.1
NET_U4_3: R12.2, R13.1, U4.3
NET_U4_4: R9.1, U4.4, U7.2
NET_U5_1: R2.1, U5.1, U5.2
PROC_ADC_IN4: U1.10, U8.2
PROC_ADC_IN6: U1.12, U8.3
VCC_S1_10V5: C10.1, C13.1, C14.1, J1.1, U3.8
VCC_TIER1_1V8: C1.1, C2.1, C3.1, C4.1, C5.1, C11.1, C12.1, C15.1, F1.2, R1.2, R3.2, R4.2, R6.2, R7.1, R9.2, R10.2, R12.1, U1.1, U1.17, U3.1, U4.6, U7.5
